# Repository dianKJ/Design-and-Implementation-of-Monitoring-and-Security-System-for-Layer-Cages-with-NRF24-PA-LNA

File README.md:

Position			:	Main Designer	

Jobdesc	:	Design and manufacturing electronic system, do testing (power, distance of NRF), Programming and installing device.

Project Type	:	Final Project.

Microcontroller	:	Arduino Nano V3.

Software (Electronics)	:	Eagle and Proteus

Software (Programming)	:	Arduino IDE

Component	:	NRF24L01+PA+LNA, Arduino Nano, DHT-11, MQ-135, YL-69

Description		  :		The final project of monitoring chicken farm with NRF24 + PA + LNA is to monitor air quality and safety. Using the MQ sensor to check ammonia levels, soil moisture sensors, humidity and temperature sensors, and proximity sensors as safety sensor. All sensor data are packaged and sent in a data packet from the enclosure to the owner's house using the NRF24L01 + PA + LNA. Owner can activate the safety mode from the receiver that placed at owner home.

Performance	:	Device run properly can measure the ammonia and another sensor. It can communicate (Transmitter and Receiver) in 800m range. Data that send is equal with data received. Device able to work continuously

Facilitator	:	Electrical Installation laboratory Gadjah Mada University	 

Link Project	:	https://bit.ly/3bQM7ig

Here The Electronic Design(EAGLE) and Hardware Design : 

From left (reciever , transmitter)

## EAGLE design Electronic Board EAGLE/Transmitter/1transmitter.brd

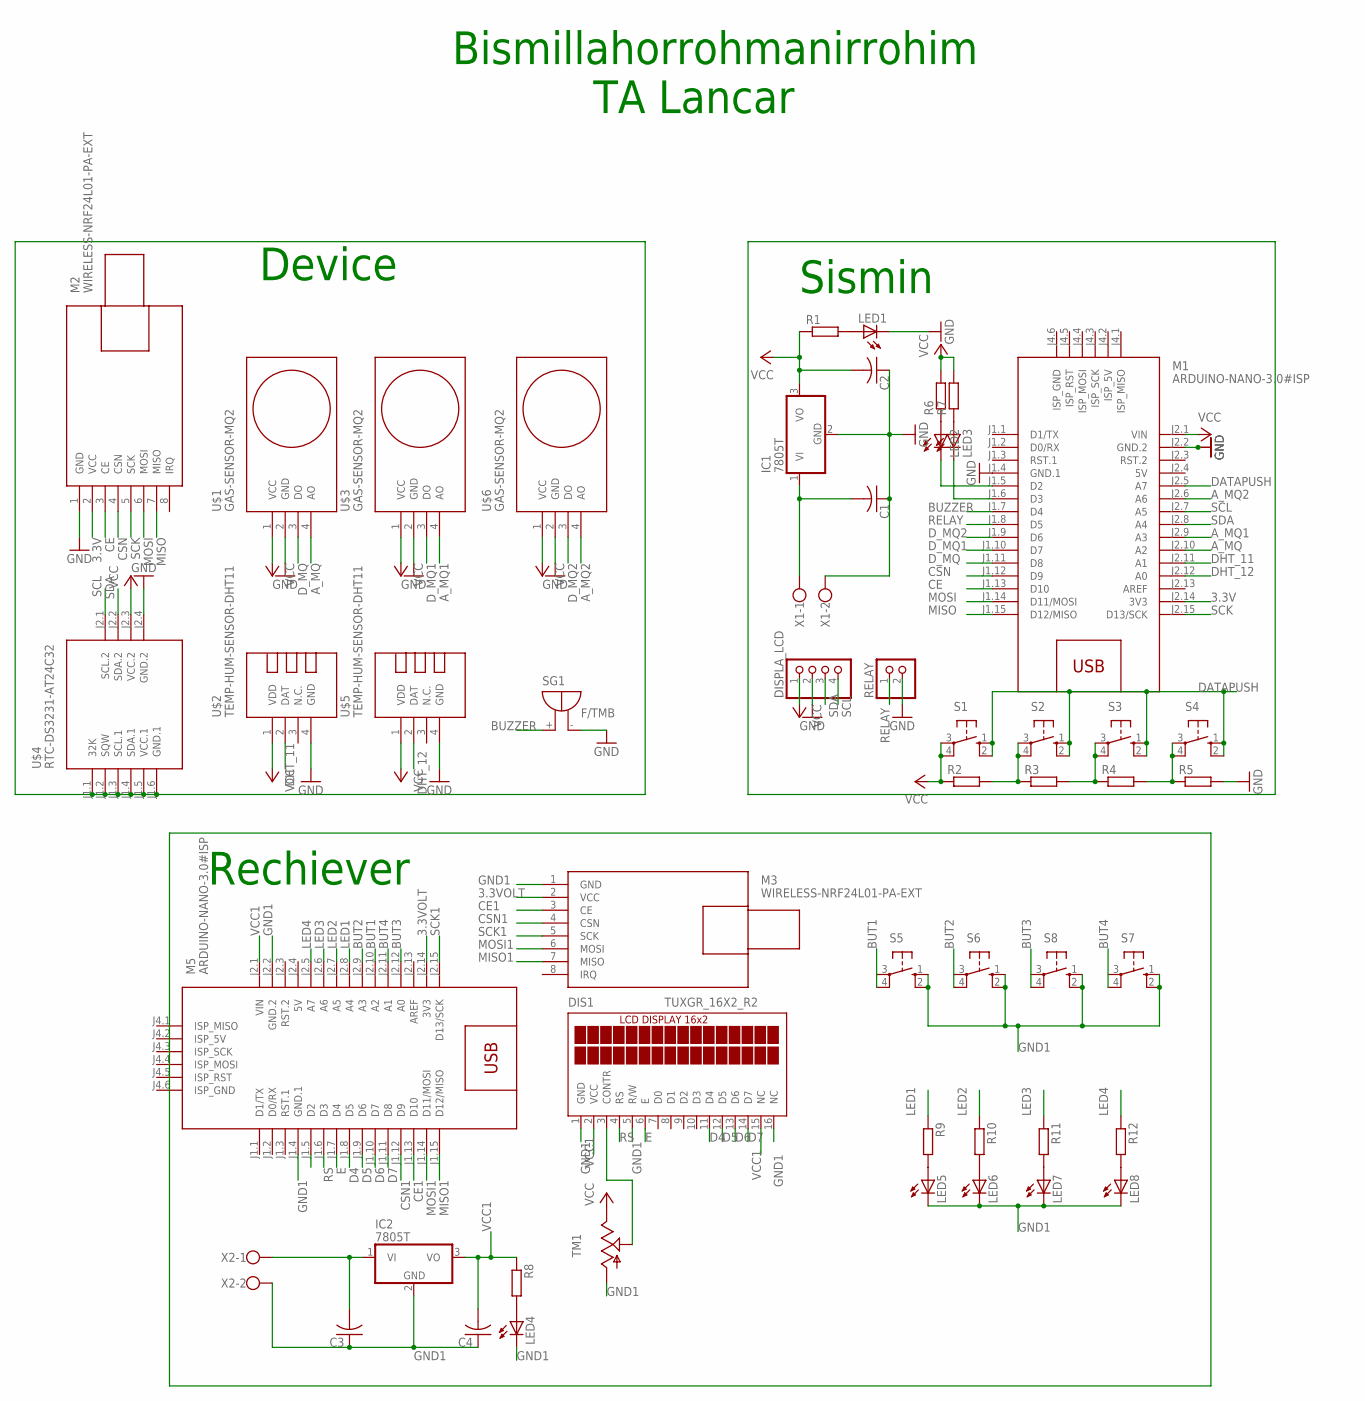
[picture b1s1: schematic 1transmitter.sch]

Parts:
C1, C2, C3, C4: C-US025-050X050; C025-050X050
DIS1: TUXGR_16X2_R2
DISPLA_LCD: PINHD-1X4; 1X04
IC1, IC2: 7805T; TO220H
LED1, LED2, LED3, LED4: LED3MM
LED5, LED6, LED7, LED8: LED5MM
M1, M5: ARDUINO-NANO-3.0#ISP
M2, M3: WIRELESS-NRF24L01-PA-EXT
R1, R2, R3, R4, R5, R6, R7, R8, R9, R10, R11, R12: R-EU_0207/7; 0207/7
RELAY: PINHD-1X2; 1X02
S1, S2, S3, S4, S5, S6, S7, S8: 10-XX; B3F-10XX
SG1: F/TMB
TM1: TRIM; 6MM
U$1, U$3, U$6: GAS-SENSOR-MQ2
U$2, U$5: TEMP-HUM-SENSOR-DHT11
U$4: RTC-DS3231-AT24C32
X1, X2: W237-102

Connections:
3.3V: M1.J2.14 (3V3), M2.2 (VCC)
3.3VOLT: M3.2 (VCC), M5.J2.14 (3V3)
5V: M1.J2.4 (5V), M5.J2.4 (5V)
A_MQ: M1.J2.10 (A2), U$1.4 (AO)
A_MQ1: M1.J2.9 (A3), U$3.4 (AO)
A_MQ2: M1.J2.6 (A6), U$6.4 (AO)
BUT1: M5.J2.10 (A2), S5.4 (P1)
BUT2: M5.J2.9 (A3), S6.4 (P1)
BUT3: M5.J2.12 (A0), S8.4 (P1)
BUT4: M5.J2.11 (A1), S7.4 (P1)
BUZZER: M1.J1.7 (D4), SG1.+
CE: M1.J1.13 (D10), M2.3 (CE)
CE1: M3.3 (CE), M5.J1.13 (D10)
CSN: M1.J1.12 (D9), M2.4 (CSN)
CSN1: M3.4 (CSN), M5.J1.12 (D9)
D4: DIS1.11 (D4), M5.J1.8 (D5)
D5: DIS1.12 (D5), M5.J1.9 (D6)
D6: DIS1.13 (D6), M5.J1.10 (D7)
D7: DIS1.14 (D7), M5.J1.11 (D8)
DATAPUSH: M1.J2.5 (A7), S1.1 (S), S1.2 (S1), S2.1 (S), S2.2 (S1), S3.1 (S), S3.2 (S1), S4.1 (S), S4.2 (S1)
DHT_11: M1.J2.11 (A1), U$2.2 (DAT)
DHT_12: M1.J2.12 (A0), U$5.2 (DAT)
D_MQ: M1.J1.11 (D8), U$1.3 (DO)
D_MQ1: M1.J1.10 (D7), U$3.3 (DO)
D_MQ2: M1.J1.9 (D6), U$6.3 (DO)
E: DIS1.6 (E), M5.J1.7 (D4)
LED1: M5.J2.8 (A4), R9.1
LED2: M5.J2.7 (A5), R10.1
LED3: M5.J2.6 (A6), R11.1
LED4: M5.J2.5 (A7), R12.1
MISO: M1.J1.15 (D12/MISO), M2.7 (MISO)
MISO1: M3.7 (MISO), M5.J1.15 (D12/MISO)
MOSI: M1.J1.14 (D11/MOSI), M2.6 (MOSI)
MOSI1: M3.6 (MOSI), M5.J1.14 (D11/MOSI)
unnamed: C1.2, IC1.1 (VI), X1.1
unnamed: LED1.A, R1.2
unnamed: U$4.J1.1 (32K), U$4.J1.2 (SQW), U$4.J1.3 (SCL.1), U$4.J1.4 (SDA.1), U$4.J1.5 (VCC.1), U$4.J1.6 (GND.1)
unnamed: LED2.A, R6.1
unnamed: R2.2, R3.1, S2.3, S2.4 (P1)
unnamed: LED3.A, R7.1
unnamed: R3.2, R4.1, S3.3, S3.4 (P1)
unnamed: LED2.K (C), M1.J1.5 (D2)
unnamed: R4.2, R5.1, S4.3, S4.4 (P1)
unnamed: LED3.K (C), M1.J1.6 (D3)
unnamed: C3.2, IC2.1 (VI), X2.1
unnamed: LED4.A, R8.2
unnamed: DIS1.3 (CONTR), TM1.S
unnamed: LED5.A, R9.2
unnamed: LED6.A, R10.2
unnamed: LED7.A, R11.2
unnamed: LED8.A, R12.2
RELAY: M1.J1.8 (D5), RELAY.1
RS: DIS1.4 (RS), M5.J1.6 (D3)
SCK: M1.J2.15 (D13/SCK), M2.5 (SCK)
SCK1: M3.5 (SCK), M5.J2.15 (D13/SCK)
SCL: DISPLA_LCD.4, M1.J2.7 (A5), U$4.J2.1 (SCL.2)
SDA: DISPLA_LCD.3, M1.J2.8 (A4), U$4.J2.2 (SDA.2)

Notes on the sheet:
Device
Sismin
Bismillahorrohmanirrohim TA Lancar
Rechiever

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
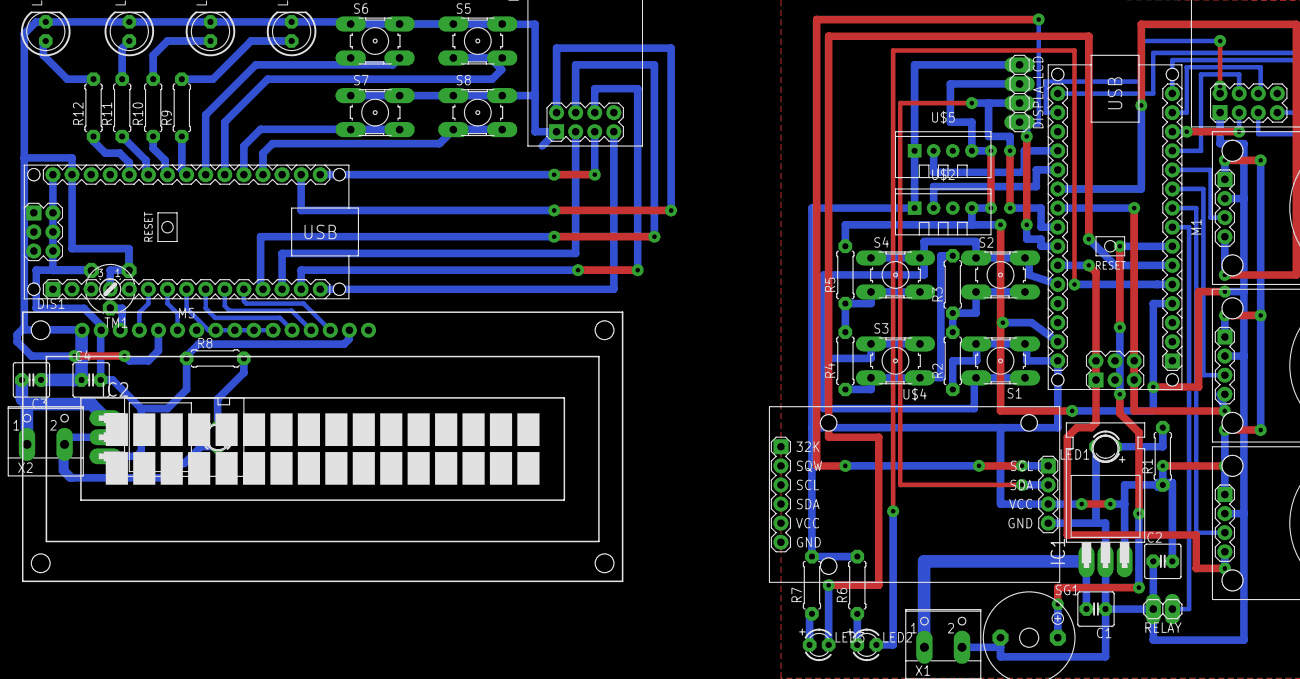
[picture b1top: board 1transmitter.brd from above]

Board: 2 copper layers, 51 parts (0 on the bottom side), 59 nets.

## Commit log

2022-05-29 Create Code Arduino IDE

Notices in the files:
parts and their libraries:
diy-modules: Released under the Creative Commons Attribution 4.0 International License: http://creativecommons.org/licenses/by/4.0
